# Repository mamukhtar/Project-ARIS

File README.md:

# Project-ARIS
A collection of programs for sensor data processing, machine learning, GPS integration, and hub-to-hub communication in a distributed system.
# Project README

This README provides an overview of the components and programs included in this GitHub repository. The repository contains various programs related to sensor data processing, machine learning, GPS journey logistics, hub-to-hub communication, server-client communication, and a Unity project for the HoloLens interface. The programs are designed to work together to facilitate data collection, analysis, and communication for ARIS an Augmented reality Informational system for astronauts. Below is a brief description of each program:

1. **Arduino Program**:
   - Uploads integrated sensors code to the Arduino Nano to allow for continuous data collection.
   - Code Written by Oussama with help from Maryam to organize the data output 
   
2. **Arduino to Pi Program**:
   - Reads sensor data from the Arduino and saves it to a new CSV file every 200 sets of data.
   - Code Written by Maryam
   
3. **Machine Learning Program**:
   - Takes the read sensor data every 180 seconds, applies machine learning techniques, and determines the status and condition based on the training set if the data is Normal or Abnormal given the status i.e. running, walking or resting. The results are appended to the original sensor data.
   - Code Written by Kalvin with help from Maryam
   
4. **GPS Module and Journey Logistics Program**:
   - Calculates the distance in kilometers and miles from the current location to predefined buildings using GPS coordinates.
   - Estimates the time required to reach the destination based on GPS speed and assumes a walking speed of 3 miles per hour.
   - Determines the consumables (oxygen, water, and battery) needed for the journey and appends the information to the full hub data file.
   - Code Written by Maryam and Kalvin
   
5. **Hub-to-Hub Program**:
   - Sends the full hub data file to the other hub in chunks of 200 bytes every 180 seconds.
   - Receives the full appended data file from the other hub and saves it locally.
   - Code Written by Maryam
   
6. **Server-Client-UnityC Programs**:
   - The Python client sends hub 1 and hub 2 CSV data files to the server every 180 seconds.
   - The server saves the received data files to separate folders for hub 1 and hub 2.
   - The Unity client receives the data and saves it to folders within the Unity project's Assets directory for display purposes.
   - Code Written by Maryam
   
7. **Hub1/2 Bash Script**:
   - Executes a sequence of Python scripts in the background with specified time intervals.
   - Some of the background processes run in an infinite loop, so the script continues until all programs are manually stopped or the computer is rebooted.
   -  Code Written by Maryam
   
8. **On/Off Program**:
   - Designed to run on a Raspberry Pi computer, this Python script controls the state of the system with a push button.
   - The script listens for button press events on a specific GPIO pin and toggles the system on/off accordingly.
   - LEDs are used to indicate the state of the system.
   - Additionally, the script starts and stops the hub1/2 bash script as per the system's state.
   -  Code Written by Maryam

Please refer to the individual program files for more detailed information, including specific setup instructions, dependencies, and usage guidelines.

The GitHub repository currently lacks detailed documentation on the electronics and sensors information (the sensor hub portion), which is essential to collect the sensor data.

Feel free to explore and utilize these programs according to your project requirements. If you have any questions or encounter any issues, please don't hesitate to reach out to us.

Enjoy working with the system!

-*Maryam Aminu Mukhtar (CE) Team Lead, 
Oussama Ourich (EE),
Felice Gabardi (EE),
Kalvin Fonseca (EE),
/Team 4*

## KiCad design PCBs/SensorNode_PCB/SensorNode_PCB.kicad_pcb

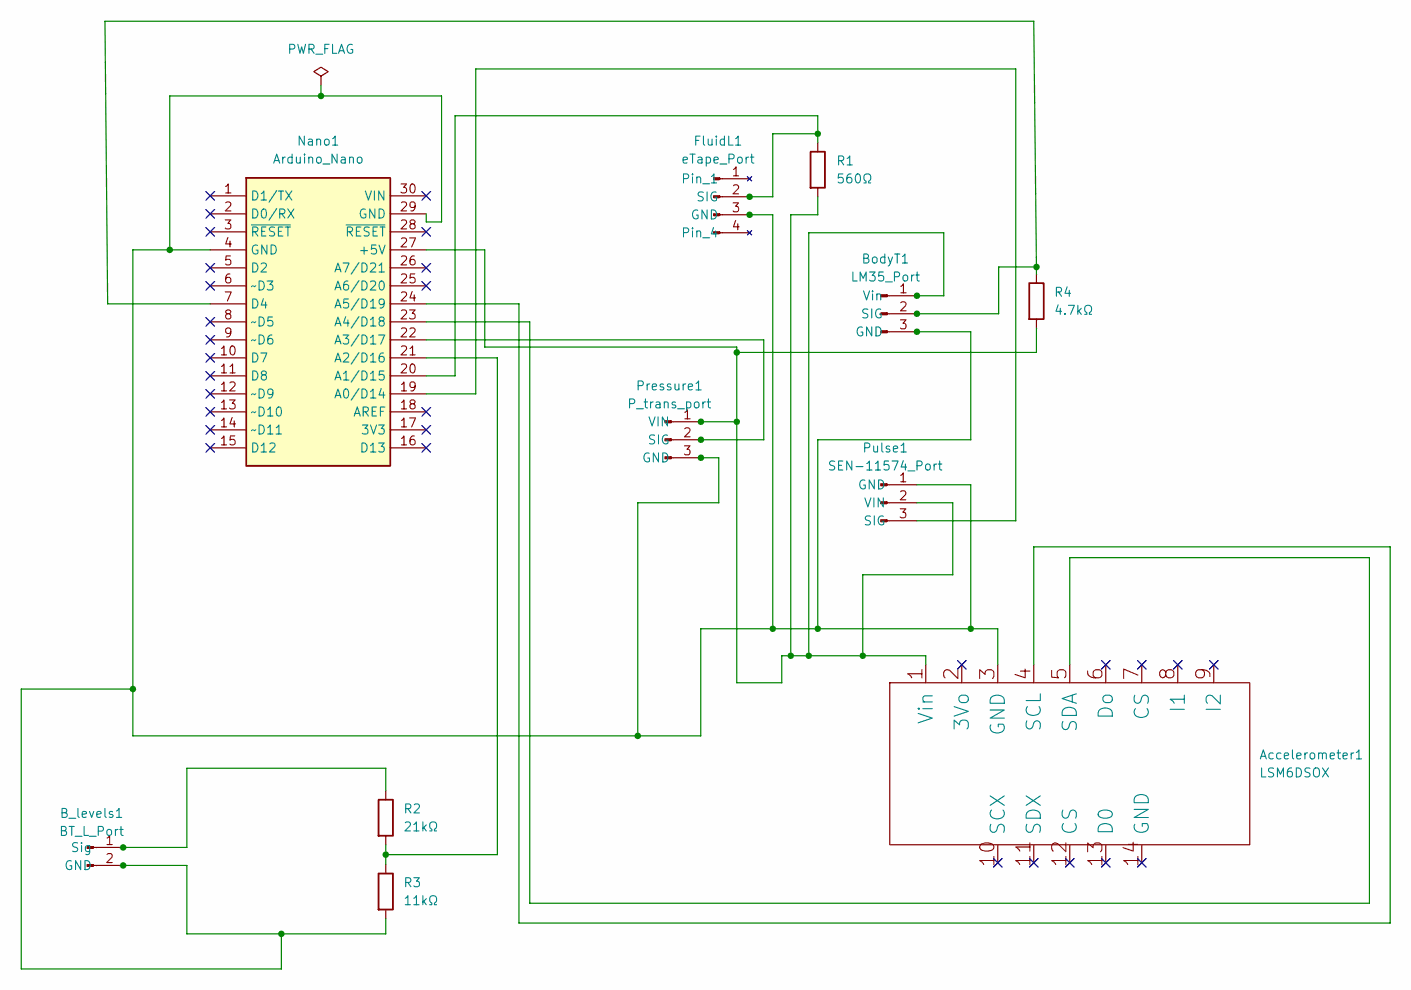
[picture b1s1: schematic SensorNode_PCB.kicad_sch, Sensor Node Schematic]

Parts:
Accelerometer1: LSM6DSOX
B_levels1: BT_L_Port; PinHeader_1x02_P2.54mm_Vertical
BodyT1: LM35_Port; PinHeader_1x03_P2.54mm_Vertical
FluidL1: eTape_Port; PinHeader_1x04_P2.54mm_Vertical
Nano1: Arduino_Nano
Pressure1: P_trans_port; PinHeader_1x03_P2.54mm_Vertical
Pulse1: SEN-11574_Port; PinHeader_1x03_P2.54mm_Vertical
R1: 560Ω; R_Axial_DIN0207_L6.3mm_D2.5mm_P7.62mm_Horizontal
R2: 21kΩ; R_Axial_DIN0207_L6.3mm_D2.5mm_P7.62mm_Horizontal
R3: 11kΩ; R_Axial_DIN0207_L6.3mm_D2.5mm_P7.62mm_Horizontal
R4: 4.7kΩ; R_Axial_DIN0207_L6.3mm_D2.5mm_P7.62mm_Horizontal

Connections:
unnamed: Accelerometer1.3 (GND), B_levels1.2 (GND), BodyT1.3 (GND), FluidL1.3 (GND), Nano1.4 (GND), Nano1.29 (GND), Pressure1.3 (GND), Pulse1.1 (GND), R3.2
unnamed: Accelerometer1.4 (SCL), Nano1.24 (A5/D19)
unnamed: Accelerometer1.5 (SDA), Nano1.23 (A4/D18)
unnamed: B_levels1.1 (Sig), R2.1
unnamed: FluidL1.2 (SIG), Nano1.20 (A1/D15), R1.1
unnamed: BodyT1.2 (SIG), Nano1.7 (D4), R4.1
unnamed: Nano1.19 (A0/D14), Pulse1.3 (SIG)
unnamed: Nano1.21 (A2/D16), R2.2, R3.1
unnamed: Nano1.22 (A3/D17), Pressure1.2 (SIG)
unnamed: Accelerometer1.1 (Vin), BodyT1.1 (Vin), Nano1.27 (+5V), Pressure1.1 (VIN), Pulse1.2 (VIN), R1.2, R4.2

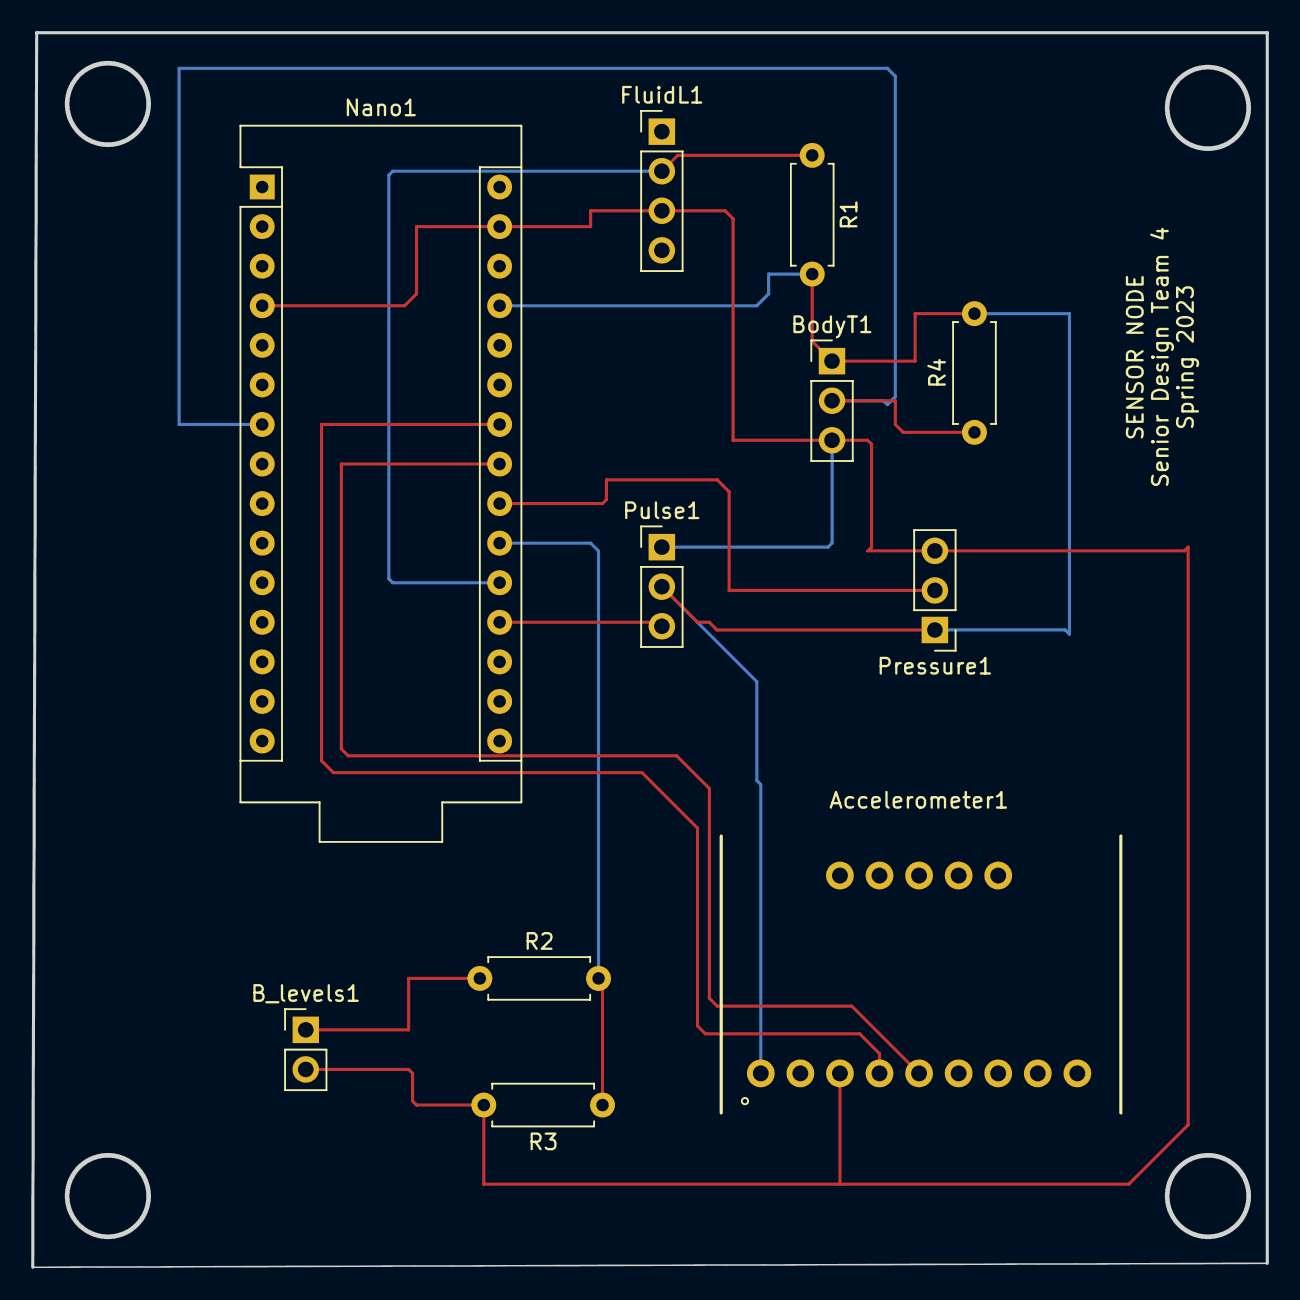
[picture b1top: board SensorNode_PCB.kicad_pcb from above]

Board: 2 copper layers, 79.2 x 79.2 mm, 11 parts (0 on the bottom side), 10 nets.

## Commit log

2023-05-15 Create xx
